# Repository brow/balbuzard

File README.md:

# Balbuzard

Balbuzard is a compact, ergonomic keyboard with 34–38 keys.

_Balbuzard 0.2 by [@smores56](https://github.com/smores56)_

## How do you type on that?
I've used Balbuzard as my main keyboard since 2019. My keymap looks like this:

_Mod 1_ and _Mod 2_ activate alternate layers of the keymap, which contain symbols, arrows, backspace, etc.

## Versions

### [0.2: Low-profile](https://github.com/brow/balbuzard/releases/tag/v0.2)

- 34–38 keys
- Compatible with Choc (low-profile) switches
- SMD diodes concealed within switches
- Silkscreen on bottom
- Tighter key spacing
- Viewing window under microcontroller
- Adjustments to positions of columns and thumb keys
- **Firmware:** [brow/qmk_firmware@balbuzard-0.2](https://github.com/brow/qmk_firmware/tree/balbuzard-0.2)

### [0.1: Classic](https://github.com/brow/balbuzard/releases/tag/v0.1)

- 36 keys
- Compatible with MX, Alps, and Choc (low-profile) switches
- Through-hole diodes nestled between switches
- Silkscreen on top
- **Firmware:** [brow/qmk_firmware@balbuzard-0.1](https://github.com/brow/qmk_firmware/tree/balbuzard-0.1)

## Using this repository

This repo contains the [Ergogen](https://github.com/mrzealot/ergogen) configuration that generates the KiCad PCB file.

Assuming you have [npm installed](https://www.npmjs.com/get-npm):

``` sh
git clone --recursive git@github.com:brow/balbuzard.git
cd balbuzard
make
```

Find the generated PCB at `output/pcbs/main.kicad_pcb`.

## More photos

_Balbuzard 0.2 with optional thumbs removed, by [@davidphilipbarr](https://github.com/davidphilipbarr)_

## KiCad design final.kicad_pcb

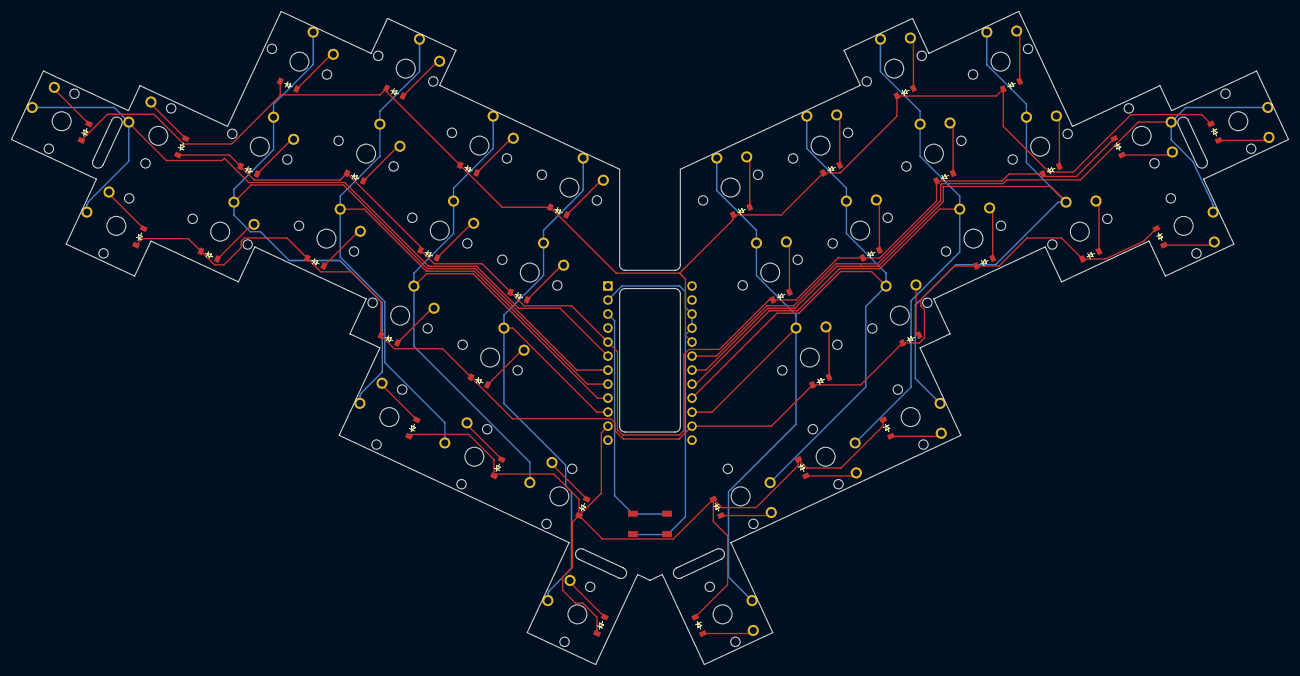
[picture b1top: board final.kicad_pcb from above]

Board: 2 copper layers, 231.5 x 118.4 mm, 77 parts (0 on the bottom side), 52 nets.

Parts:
B1: SW_TACT_ALPS_SKQGABE010
D1, D2, D3, D4, D5, D6, D7, D8, D9, D10, D11, D12, D13, D14, D15, D16, D17, D18, D19, D20, D21, D22, D23, D24, D25, D26, D27, D28, D29, D30, D31, D32, D33, D34, D35, D36, D37, D38: ComboDiode
S1, S2, S3, S4, S5, S6, S7, S8, S9, S10, S11, S12, S13, S14, S15, S16, S17, S18, S19, S20, S21, S22, S23, S24, S25, S26, S27, S28, S29, S30, S31, S32, S33, S34, S35, S36, S37, S38: PG1350

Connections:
P2: D3.1, D6.1, D9.1, D12.1, D15.1, D22.1, D25.1, D28.1, D31.1, D34.1
P3: S20.2, S21.2, S22.2
P4: S23.2, S24.2, S25.2, S35.2
P5: S26.2, S27.2, S28.2, S36.2
P6: S29.2, S30.2, S31.2, S37.2
P7: S32.2, S33.2, S34.2, S38.2
P8: D1.1, D4.1, D7.1, D10.1, D13.1, D20.1, D23.1, D26.1, D29.1, D32.1
P14: S13.2, S14.2, S15.2, S19.2
P15: S10.2, S11.2, S12.2, S18.2
P16: D16.1, D17.1, D18.1, D19.1, D35.1, D36.1, D37.1, D38.1
P18: S7.2, S8.2, S9.2, S17.2
P19: S4.2, S5.2, S6.2, S16.2
P20: S1.2, S2.2, S3.2
P21: D2.1, D5.1, D8.1, D11.1, D14.1, D21.1, D24.1, D27.1, D30.1, D33.1
far_thumb: D19.2, S19.1
home_thumb: D18.2, S18.1
index_bottom: D10.2, S10.1
index_home: D11.2, S11.1
index_top: D12.2, S12.1
inner_bottom: D13.2, S13.1
inner_home: D14.2, S14.1
inner_top: D15.2, S15.1
middle_bottom: D7.2, S7.1
middle_home: D8.2, S8.1
middle_top: D9.2, S9.1
mirror_far_thumb: D38.2, S38.1
mirror_home_thumb: D37.2, S37.1
mirror_index_bottom: D29.2, S29.1
mirror_index_home: D30.2, S30.1
mirror_index_top: D31.2, S31.1
mirror_inner_bottom: D32.2, S32.1
mirror_inner_home: D33.2, S33.1
mirror_inner_top: D34.2, S34.1
mirror_middle_bottom: D26.2, S26.1
mirror_middle_home: D27.2, S27.1
mirror_middle_top: D28.2, S28.1
mirror_near_thumb: D36.2, S36.1
mirror_nearer_thumb: D35.2, S35.1
mirror_pinky_bottom: D20.2, S20.1
mirror_pinky_home: D21.2, S21.1
mirror_pinky_top: D22.2, S22.1
mirror_ring_bottom: D23.2, S23.1
mirror_ring_home: D24.2, S24.1
mirror_ring_top: D25.2, S25.1
near_thumb: D17.2, S17.1
nearer_thumb: D16.2, S16.1
pinky_bottom: D1.2, S1.1
pinky_home: D2.2, S2.1
pinky_top: D3.2, S3.1
ring_bottom: D4.2, S4.1
ring_home: D5.2, S5.1
ring_top: D6.2, S6.1

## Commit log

2020-11-26 source files
2020-11-26 add makefile
2020-11-26 add .gitignore
2020-11-26 add ergogen submodule
2020-11-26 add README
2020-11-26 tweak README
2020-11-26 add images to README
2020-11-26 reduce image size
2020-12-17 add "How do you type on that?" section
2020-12-18 remove MX & Alps footprints
2020-12-20 choc spacing
2020-12-20 fourth thumb key
2020-12-20 adjust thumb key horizontal shifts
2020-12-20 make out column top pinky key
2020-12-21 tighten switch size to 13.7 mm
2020-12-24 shift outer pinky keys up
2020-12-27 use MBK keycap size in mockup
2020-12-27 rotate outer key 90 degrees
2020-12-27 rotate thumb keys
2020-12-27 refactor: _more_glue -> _notch
2020-12-27 shift far thumb keys centerward
2020-12-27 shift controller up
2020-12-28 rotate pinky column keys 90 degrees
2020-12-31 add perforations
2020-12-31 remove redundant spreads
2020-12-31 new default diode placement
2020-12-31 simulate LED hole diode position
2020-12-31 new matrix
2021-01-01 position diode in center of LED hole
2021-01-01 refactor using aliases
2021-01-01 round inner corners of notch
2021-01-01 controller window
2021-01-01 reset switch
2021-01-02 update silkscreen
2021-01-02 remove backside silks
2022-01-01 flesh out README, including more images
2022-01-01 tweaks to make README look nice on GitHub
2022-01-01 add photo credit to README
2022-01-01 add "More photos" to README
2022-07-08 add links to QMK firmware
    Closes #2.
2022-07-08 add links to QMK firmware (#3)
    Closes #2.
